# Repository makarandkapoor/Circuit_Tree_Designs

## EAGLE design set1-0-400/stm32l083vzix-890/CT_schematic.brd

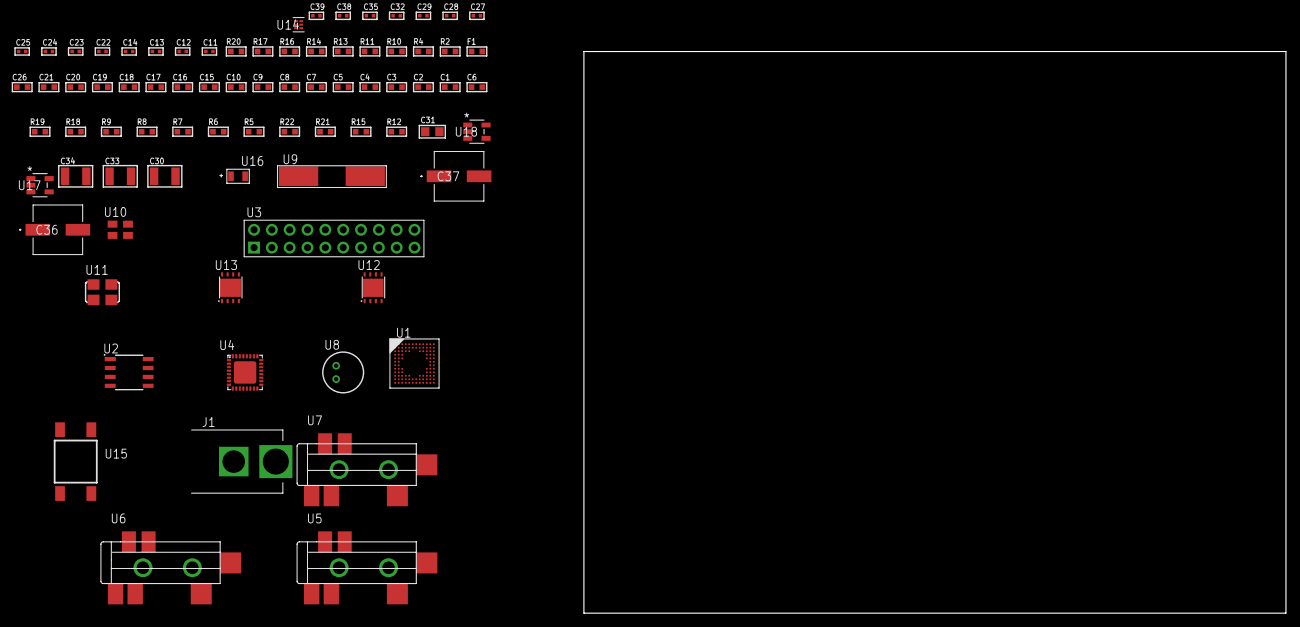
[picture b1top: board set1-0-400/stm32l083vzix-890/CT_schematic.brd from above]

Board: 2 copper layers, 100.0 x 80.0 mm, 79 parts (0 on the bottom side), 48 nets, no tracks yet.

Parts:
C1, C2, C3, C4, C5, C7, C10: 1e-07; C0603
C6: 4.7e-06; C0603
C8: 1e-08; C0603
C9, C15, C16, C17, C18, C19, C20, C21, C26: 1e-06; C0603
C11, C12: 1e-11; C0402
C13, C27, C28, C29, C32, C38, C39: 1e-08; C0402
C14, C22, C23, C24, C25, C35: 1e-07; C0402
C30, C33, C34: 1e-05; C1210
C31: 1e-05; C0805
C36, C37: 0.0001; EXV-9H
F1: 240.0; L0603
J1: PJ-037B; PJ-037B_PACKAGE
R2, R14, R17: 1000.0; R0603
R4: 4700.0; R0603
R5, R6, R7, R8, R9, R18, R19: 10000.0; R0603
R10, R11: 1270.0; R0603
R12, R15: 100000.0; R0603
R13: 200.0; R0603
R16: 2231.0; R0603
R20: 9100.0; R0603
R21: 680000.0; R0603
R22: 120000.0; R0603
U1: STM32L083VZI6; UFBGA100
U2: AT25M02-SSHD-T; SOIC-8
U3: TST-110-05-T-D-RA
U4: SGTL5000XNAA3; QFN-32
U5, U6, U7: SJ-43515TS-SMT-TR
U8: WM-64PCT; WM-64PC
U9: ABLS-25.000MHZ-B2F-T
U10: ASEK-32.768KHz-ECST; ASEK
U11: ASFL-24.57MHZ-NCS; ASFL1
U12, U13: LP3878SDX-ADJ/NOPB; WSON-8
U14: TPS3895ADRYR; SON-6
U15: 4-1437565-2; SW_4-1437565-2
U16: Q65110A2395; LGM67K-G1J2-24-Z
U17, U18: nc7sz125m5x; NC7SZ125M5X

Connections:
CLK_CRYSTAL_U1_F1: C11.1, U1.F1, U9.1
CLK_CRYSTAL_U1_G1: C12.1, U1.G1, U9.2
CLK_U1_D1: U1.D1, U10.3
CLK_U4_21: U4.21, U11.3
GND: C1.2, C2.2, C3.2, C4.2, C5.2, C6.2, C7.2, C8.2, C9.2, C10.2, C11.2, C12.2, C13.2, C14.2, C22.2, C23.2, C24.2, C25.2, C26.2, C27.2, C28.2, C29.2, C30.2, C31.2, C32.2, C33.2, C34.2, C35.2, C36.2, C37.2, C38.2, C39.2, J1.2, R2.2, R5.2, R11.2, R14.2, R17.2, R20.2, R22.2, U1.D3, U1.E3, U1.F11, U1.F12, U1.J1, U1.K1, U2.4, U3.4, U3.6, U3.8, U3.10, U3.12, U3.14, U3.16, U3.18, U3.20, U4.1, U4.3, U4.7, U4.EXP, U6.1, U7.1, U8.2, U10.2, U11.2, U12.3, U12.PAD, U13.3, U13.PAD, U14.2, U16.C, U17.2, U17.3, U18.1, U18.3
NET_U1_A4: R5.1, U1.A4
NET_U1_E2: C7.1, U1.E2
NET_U1_H2: R4.1, U1.H2, U18.4
NET_U1_M1: C8.1, C9.1, F1.1, U1.L1, U1.M1
NET_U1_M12: U15.3, U15.4
NET_U2_3: R6.1, U2.3
NET_U2_7: R8.1, U2.7
NET_U4_10: C25.1, U4.10
NET_U4_29: R10.1, U4.29
NET_U4_31: R11.1, U4.31
NET_U5_1: U4.4, U5.1
NET_U5_2: U4.2, U5.2
NET_U5_5: U4.6, U5.5
NET_U6_2: C16.1, U6.2
NET_U6_5: C15.1, U6.5
NET_U7_2: C18.1, C19.1, U7.2
NET_U7_5: C17.1, U7.5
NET_U7_13: C18.2, C19.2
NET_U8_1: C20.1, C21.1, C26.1, U4.16, U8.1
NET_U8_15: C20.2, C21.2
NET_U12_1: C29.1, U12.1
NET_U12_6: R13.2, R14.1, U12.6
NET_U12_8: R12.1, U12.8
NET_U13_1: C32.1, U13.1
NET_U13_6: R16.2, R17.1, U13.6
NET_U13_8: R15.1, U13.8
NET_U14_1: R19.1, R20.1, U14.1
NET_U14_3: R21.2, R22.1, U14.3
NET_U14_4: R18.1, U14.4, U17.4, U18.2
NET_U15_1: R2.1, U15.1, U15.2
PROC_I2S2_CK: U1.B9, U4.24
PROC_I2S2_SD: U1.B7, U4.26
PROC_I2S2_WS: U1.B3, U4.23
PROC_SPI1_MISO: U1.A7, U2.2
PROC_SPI1_MOSI: U1.A12, U2.5
PROC_SPI1_NSS: R7.1, U1.A9, U2.1
PROC_SPI1_SCK: U1.A8, U2.6
PROC_SYS_SWCLK: U1.A10, U3.9
PROC_SYS_SWDIO: U1.A11, U3.7
RST_OUT_U3_SRESET_B: R9.1, U3.15, U17.1
VCC_S1_13V1: C30.1, C33.1, C36.1, C37.1, J1.1, R12.2, R15.2, U12.4, U13.4
VCC_TIER1_1V2: C22.1, C31.1, R13.1, U4.30, U12.5
VCC_TIER1_3V3: C1.1, C2.1, C3.1, C4.1, C5.1, C6.1, C10.1, C13.1, C14.1, C23.1, C24.1, C27.1, C28.1, C34.1, C35.1, C38.1, C39.1, F1.2, R4.2, R6.2, R7.2, R8.2, R9.2, R10.2, R16.1, R18.2, R19.2, R21.1, U1.C4, U1.C11, U1.G11, U1.G12, U1.H3, U2.8, U3.1, U4.5, U4.20, U10.4, U11.4, U13.5, U14.6, U17.5, U18.5

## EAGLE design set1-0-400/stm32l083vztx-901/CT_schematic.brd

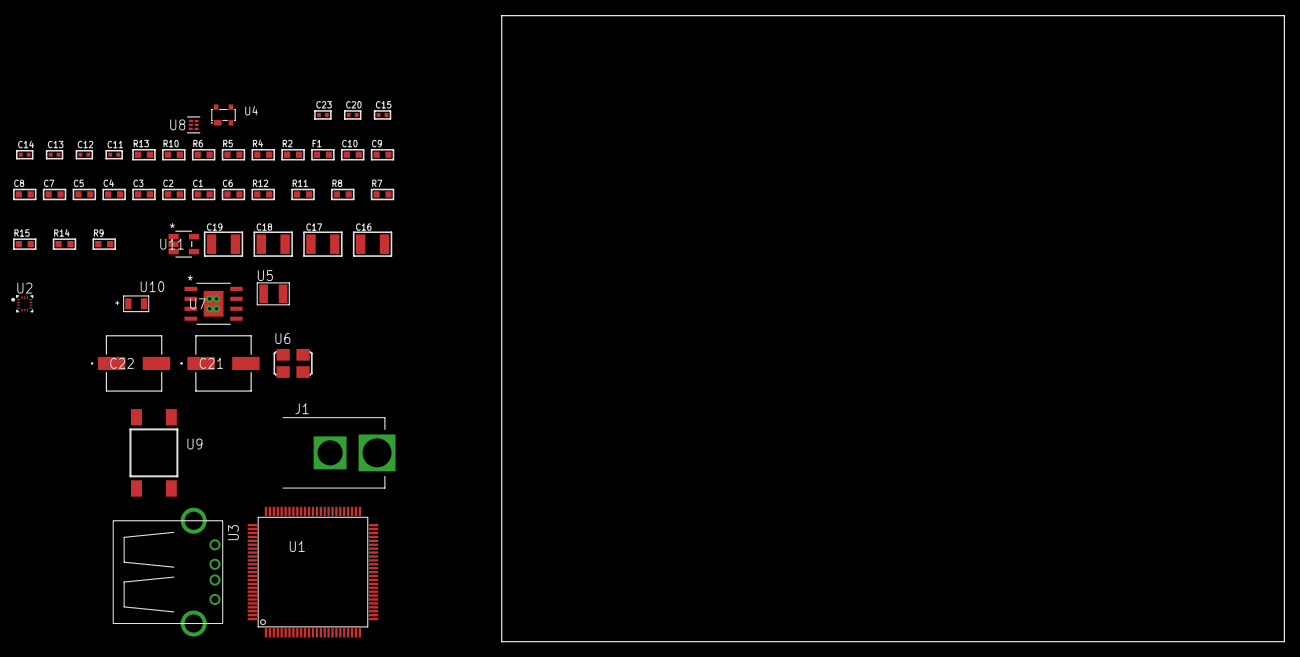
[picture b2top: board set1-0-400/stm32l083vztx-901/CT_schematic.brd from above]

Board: 2 copper layers, 100.0 x 80.0 mm, 49 parts (0 on the bottom side), 21 nets, no tracks yet.

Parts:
C1, C2, C3, C4, C5, C7, C10: 1e-07; C0603
C6: 4.7e-06; C0603
C8: 1e-08; C0603
C9: 1e-06; C0603
C11, C12: 1e-11; C0402
C13, C14, C20: 1e-07; C0402
C15, C23: 1e-08; C0402
C16, C17, C18, C19: 1e-05; C1210
C21, C22: 0.0001; EXV-9H
F1: 240.0; L0603
J1: PJ-037B; PJ-037B_PACKAGE
R2: 1000.0; R0603
R4: 4700.0; R0603
R5, R6, R10: 2200.0; R0603
R7, R8, R11, R12: 10000.0; R0603
R9: 4031.5447154472; R0603
R13: 9100.0; R0603
R14: 680000.0; R0603
R15: 120000.0; R0603
U1: STM32L083VZT6; LQFP100
U2: BMC150; LGA14R35P5X6_200X200X100
U3: 61400416021; USB-A-H
U4: prtr5v0u2ax; SOT143B
U5: ABS07-32.768KHZ-7-T
U6: ASFL1-25MHZ-NCS; ASFL1
U7: MIC5234YME; SOIC-8_EP
U8: TPS3895ADRYR; SON-6
U9: 4-1437565-2; SW_4-1437565-2
U10: Q65110A2395; LGM67K-G1J2-24-Z
U11: nc7sz125m5x; NC7SZ125M5X

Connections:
CLK_CRYSTAL_U1_8: C11.1, U1.8, U5.1
CLK_CRYSTAL_U1_9: C12.1, U1.9, U5.2
CLK_U1_12: U1.12, U6.3
GND: C1.2, C2.2, C3.2, C4.2, C5.2, C6.2, C7.2, C8.2, C9.2, C10.2, C11.2, C12.2, C13.2, C14.2, C15.2, C16.2, C17.2, C18.2, C19.2, C20.2, C21.2, C22.2, C23.2, J1.2, R2.2, R7.2, R10.2, R13.2, R15.2, U1.19, U1.20, U1.27, U1.49, U1.74, U1.99, U2.1, U2.6, U2.7, U2.9, U3.4, U3.5, U3.6, U4.1, U6.2, U7.7, U7.EPAD, U8.2, U10.C, U11.1, U11.3
NET_U1_6: C7.1, U1.6
NET_U1_14: R4.1, U1.14, U11.4
NET_U1_22: C8.1, C9.1, F1.1, U1.21, U1.22
NET_U1_68: R5.1, U1.68, U2.11
NET_U1_69: R6.1, U1.69, U2.14
NET_U1_94: R7.1, U1.94
NET_U1_98: U9.3, U9.4
NET_U4_4: U3.1, U4.4
NET_U7_4: R9.2, R10.1, U7.4
NET_U8_1: R12.1, R13.1, U8.1
NET_U8_3: R14.2, R15.1, U8.3
NET_U8_4: R11.1, U8.4, U11.2
NET_U9_1: R2.1, U9.1, U9.2
PROC_USB_DM: U1.70, U3.2, U4.3
PROC_USB_DP: U1.71, U3.3, U4.2
VCC_S1_16V3: C16.1, C17.1, C21.1, C22.1, J1.1, U7.5, U7.8
VCC_TIER1_3V3: C1.1, C2.1, C3.1, C4.1, C5.1, C6.1, C10.1, C13.1, C14.1, C15.1, C18.1, C19.1, C20.1, C23.1, F1.2, R4.2, R5.2, R6.2, R8.1, R8.2, R9.1, R11.2, R12.2, R14.1, U1.28, U1.50, U1.73, U1.75, U1.100, U2.8, U2.10, U2.12, U2.13, U6.4, U7.1, U8.6, U11.5

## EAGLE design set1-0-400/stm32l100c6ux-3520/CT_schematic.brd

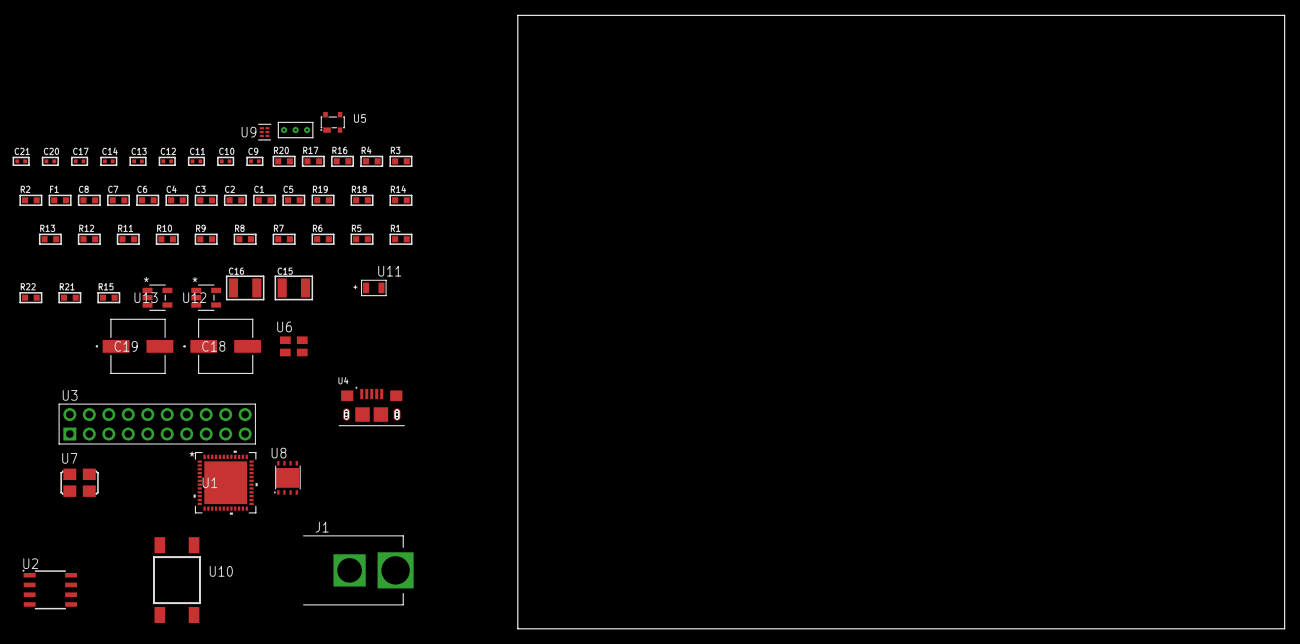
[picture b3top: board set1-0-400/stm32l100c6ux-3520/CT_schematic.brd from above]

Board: 2 copper layers, 122.6 x 80.0 mm, 59 parts (0 on the bottom side), 36 nets, no tracks yet.

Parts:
C1, C2, C3, C4, C6: 1e-07; C0603
C5: 4.7e-06; C0603
C7: 1e-08; C0603
C8: 1e-06; C0603
C9, C12, C13, C14, C20, C21: 1e-08; C0402
C10, C11, C17: 1e-07; C0402
C15, C16: 1e-05; C1210
C18, C19: 0.0001; EXV-9H
F1: 240.0; L0603
J1: PJ-037B; PJ-037B_PACKAGE
R1, R5, R6, R7, R8, R9, R10, R11, R12, R13, R14, R18, R19: 10000.0; R0603
R2, R17: 1000.0; R0603
R3: 1600.5; R0603
R4: 4700.0; R0603
R15: 100000.0; R0603
R16: 2231.0; R0603
R20: 9100.0; R0603
R21: 680000.0; R0603
R22: 120000.0; R0603
U1: STM32L100C6U6; UFQFPN48
U2: AT25640B-SSHL-T; SOIC-8
U3: TST-110-05-T-D-RA
U4: 10118193-0001LF; FCI_10118193-0001LF
U5: prtr5v0u2ax; SOT143B
U6: ASEK-32.768KHz-ECST; ASEK
U7: ASFL1-25MHZ-NCS; ASFL1
U8: LP3878SDX-ADJ/NOPB; WSON-8
U9: TPS3895ADRYR; SON-6
U10: 4-1437565-2; SW_4-1437565-2
U11: Q65110A2395; LGM67K-G1J2-24-Z
U12, U13: nc7sz125m5x; NC7SZ125M5X
U14: Dummy; DUMMY_PACKAGE_125

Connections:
CLK_U1_3: U1.3, U6.3
CLK_U1_5: U1.5, U7.3
GND: C1.2, C2.2, C3.2, C4.2, C5.2, C6.2, C7.2, C8.2, C9.2, C10.2, C11.2, C12.2, C13.2, C14.2, C15.2, C16.2, C17.2, C18.2, C19.2, C20.2, C21.2, J1.2, R2.2, R5.2, R14.2, R17.2, R20.2, R22.2, U1.8, U1.23, U1.35, U1.47, U1.49, U2.4, U3.4, U3.6, U3.8, U3.10, U3.12, U3.14, U3.16, U3.18, U3.20, U4.5, U4.6, U4.7, U4.8, U4.9, U5.1, U6.2, U7.2, U8.3, U8.PAD, U9.2, U11.C, U12.2, U12.3, U13.1, U13.3, U14.1
NET_U1_1: C6.1, U1.1
NET_U1_7: R4.1, U1.7, U13.4
NET_U1_9: C7.1, C8.1, F1.1, U1.9
NET_U1_44: R5.1, U1.44
NET_U1_45: R3.1, U1.45, U11.A
NET_U1_46: R1.1, U1.46, U10.3, U10.4
NET_U2_3: R6.1, U2.3
NET_U2_7: R8.1, U2.7
NET_U3_19: R14.1, U3.19
NET_U5_4: U4.1, U5.4
NET_U8_1: C14.1, U8.1
NET_U8_6: R16.2, R17.1, U8.6
NET_U8_8: R15.1, U8.8
NET_U9_1: R19.1, R20.1, U9.1
NET_U9_3: R21.2, R22.1, U9.3
NET_U9_4: R18.1, U9.4, U12.4, U13.2
NET_U10_1: R2.1, U10.1, U10.2
PROC_SPI1_MISO: U1.16, U2.2
PROC_SPI1_MOSI: U1.17, U2.5
PROC_SPI1_NSS: R7.1, U1.14, U2.1
PROC_SPI1_SCK: U1.15, U2.6
PROC_SYS_JTCK_SWCLK: R12.1, U1.37, U3.9
PROC_SYS_JTDI: R10.1, U1.38, U3.5
PROC_SYS_JTDO_TRACESWO: U1.39, U3.13
PROC_SYS_JTMS_SWDIO: R11.1, U1.34, U3.7
PROC_SYS_JTRST: R9.1, U1.40, U3.3
PROC_TIM2_CH1: U1.10, U14.3
PROC_TIM2_CH3: U1.12, U14.2
PROC_USB_DM: U1.32, U4.2, U5.3
PROC_USB_DP: U1.33, U4.3, U5.2
RST_OUT_U3_SRESET_B: R13.1, U3.15, U12.1
VCC_S1_15V6: C15.1, C18.1, C19.1, J1.1, R15.2, U8.4
VCC_TIER1_3V3: C1.1, C2.1, C3.1, C4.1, C5.1, C9.1, C10.1, C11.1, C12.1, C13.1, C16.1, C17.1, C20.1, C21.1, F1.2, R1.2, R3.2, R4.2, R6.2, R7.2, R8.2, R9.2, R10.2, R11.2, R12.2, R13.2, R16.1, R18.2, R19.2, R21.1, U1.24, U1.36, U1.48, U2.8, U3.1, U3.2, U6.4, U7.4, U8.5, U9.6, U12.5, U13.5

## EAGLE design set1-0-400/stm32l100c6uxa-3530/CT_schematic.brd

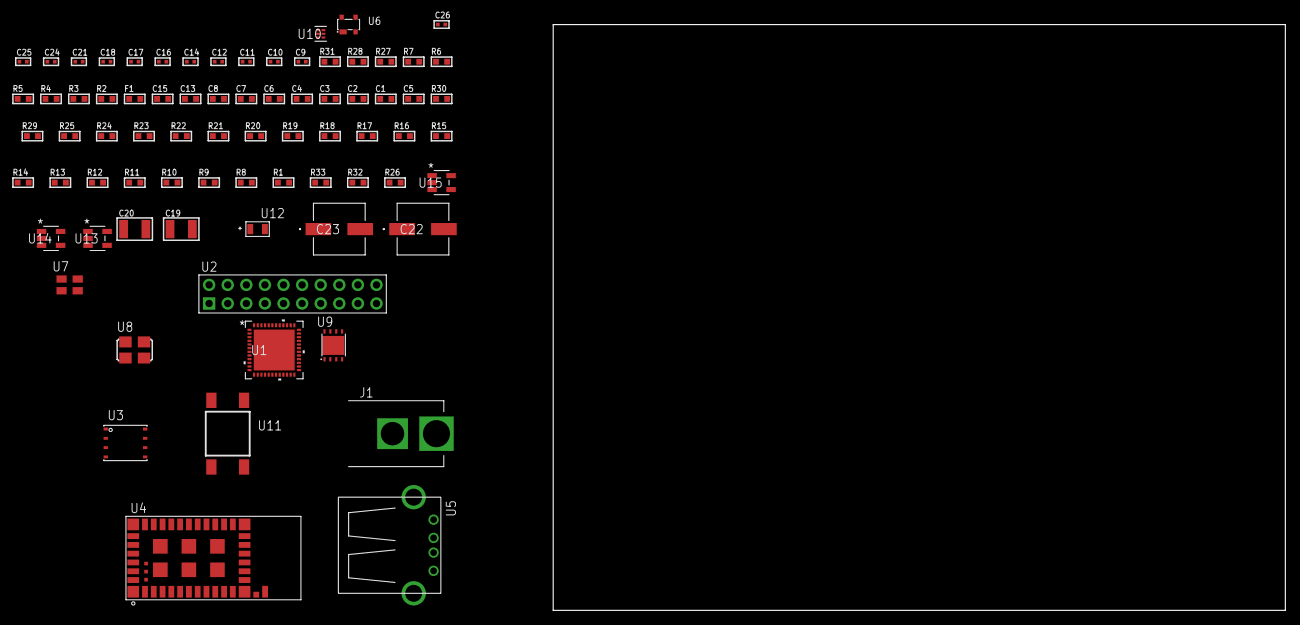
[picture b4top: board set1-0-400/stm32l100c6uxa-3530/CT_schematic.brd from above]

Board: 2 copper layers, 100.0 x 80.0 mm, 76 parts (0 on the bottom side), 42 nets, no tracks yet.

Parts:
C1, C2, C3, C4, C6: 1e-07; C0603
C5: 4.7e-06; C0603
C7: 1e-08; C0603
C8, C13, C15: 1e-06; C0603
C9, C10, C12, C14, C21: 1e-07; C0402
C11, C16, C17, C18, C24, C25, C26: 1e-08; C0402
C19, C20: 1e-05; C1210
C22, C23: 0.0001; EXV-9H
F1: 240.0; L0603
J1: PJ-037B; PJ-037B_PACKAGE
R1, R8, R9, R10, R11, R12, R13, R14, R15, R16, R17, R18, R25, R29, R30: 10000.0; R0603
R2, R28: 1000.0; R0603
R3: 1600.5; R0603
R4, R5: 4700.0; R0603
R6, R7: 2200.0; R0603
R19, R20, R21, R22, R23, R24: 34000.0; R0603
R26: 100000.0; R0603
R27: 2231.0; R0603
R31: 9100.0; R0603
R32: 680000.0; R0603
R33: 120000.0; R0603
U1: STM32L100C6U6A; UFQFPN48
U2: TST-110-05-T-D-RA
U3: 24AA512-I/MF; DFN8-S
U4: 88-00153-02
U5: 61400416021; USB-A-H
U6: prtr5v0u2ax; SOT143B
U7: ASEK-32.768KHz-ECST; ASEK
U8: ASFL1-25MHZ-NCS; ASFL1
U9: LP3878SDX-ADJ/NOPB; WSON-8
U10: TPS3895ADRYR; SON-6
U11: 4-1437565-2; SW_4-1437565-2
U12: Q65110A2395; LGM67K-G1J2-24-Z
U13, U14, U15: nc7sz125m5x; NC7SZ125M5X

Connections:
CLK_U1_3: U1.3, U7.3
CLK_U1_5: U1.5, U8.3
GND: C1.2, C2.2, C3.2, C4.2, C5.2, C6.2, C7.2, C8.2, C9.2, C10.2, C11.2, C12.2, C13.2, C14.2, C15.2, C16.2, C17.2, C18.2, C19.2, C20.2, C21.2, C22.2, C23.2, C24.2, C25.2, C26.2, J1.2, R2.2, R8.2, R14.2, R15.2, R16.2, R28.2, R31.2, R33.2, U1.8, U1.23, U1.35, U1.47, U1.49, U2.4, U2.6, U2.8, U2.10, U2.12, U2.14, U2.16, U2.18, U2.20, U3.4, U3.7, U4.1, U4.9, U4.13, U4.14, U4.15, U4.16, U4.17, U4.18, U4.19, U4.20, U4.21, U4.22, U4.23, U4.24, U4.25, U4.26, U4.27, U4.31, U4.32, U4.39, U4.40, U4.41, U4.42, U4.43, U4.44, U4.49, U5.4, U5.5, U5.6, U6.1, U7.2, U8.2, U9.3, U9.PAD, U10.2, U12.C, U13.2, U13.3, U14.1, U14.3, U15.1, U15.3
NET_U1_1: C6.1, U1.1
NET_U1_7: R5.1, U1.7, U15.4
NET_U1_9: C7.1, C8.1, F1.1, U1.9
NET_U1_42: R6.1, U1.42, U3.6
NET_U1_43: R7.1, U1.43, U3.5
NET_U1_44: R8.1, U1.44
NET_U1_45: R3.1, U1.45, U12.A
NET_U1_46: R1.1, U1.46, U11.3, U11.4
NET_U2_19: R14.1, U2.19
NET_U3_1: R15.1, U3.1
NET_U3_2: R16.1, U3.2
NET_U3_3: R17.1, U3.3
NET_U4_2: R21.1, U4.2
NET_U4_6: R25.1, U4.6
NET_U4_10: R4.1, U4.10, U14.4
NET_U4_11: R18.1, U4.11
NET_U4_34: R20.1, U4.34
NET_U6_4: U5.1, U6.4
NET_U9_1: C18.1, U9.1
NET_U9_6: R27.2, R28.1, U9.6
NET_U9_8: R26.1, U9.8
NET_U10_1: R30.1, R31.1, U10.1
NET_U10_3: R32.2, R33.1, U10.3
NET_U10_4: R29.1, U10.4, U13.4, U14.2, U15.2
NET_U11_1: R2.1, U11.1, U11.2
PROC_SPI1_MISO: R19.1, U1.16, U4.35
PROC_SPI1_MOSI: R23.1, U1.17, U4.37
PROC_SPI1_NSS: R22.1, U1.14, U4.38
PROC_SPI1_SCK: R24.1, U1.15, U4.36
PROC_SYS_JTCK_SWCLK: R12.1, U1.37, U2.9
PROC_SYS_JTDI: R10.1, U1.38, U2.5
PROC_SYS_JTDO_TRACESWO: U1.39, U2.13
PROC_SYS_JTMS_SWDIO: R11.1, U1.34, U2.7
PROC_SYS_JTRST: R9.1, U1.40, U2.3
PROC_USB_DM: U1.32, U5.2, U6.3
PROC_USB_DP: U1.33, U5.3, U6.2
RST_OUT_U2_SRESET_B: R13.1, U2.15, U13.1
VCC_S1_14V6: C19.1, C22.1, C23.1, J1.1, R26.2, U9.4
VCC_TIER1_3V3: C1.1, C2.1, C3.1, C4.1, C5.1, C9.1, C10.1, C11.1, C12.1, C13.1, C14.1, C15.1, C16.1, C17.1, C20.1, C21.1, C24.1, C25.1, C26.1, F1.2, R1.2, R3.2, R4.2, R5.2, R6.2, R7.2, R9.2, R10.2, R11.2, R12.2, R13.2, R17.2, R18.2, R19.2, R20.2, R21.2, R22.2, R23.2, R24.2, R25.2, R27.1, R29.2, R30.2, R32.1, U1.24, U1.36, U1.48, U2.1, U2.2, U3.8, U4.12, U4.33, U7.4, U8.4, U9.5, U10.6, U13.5, U14.5, U15.5

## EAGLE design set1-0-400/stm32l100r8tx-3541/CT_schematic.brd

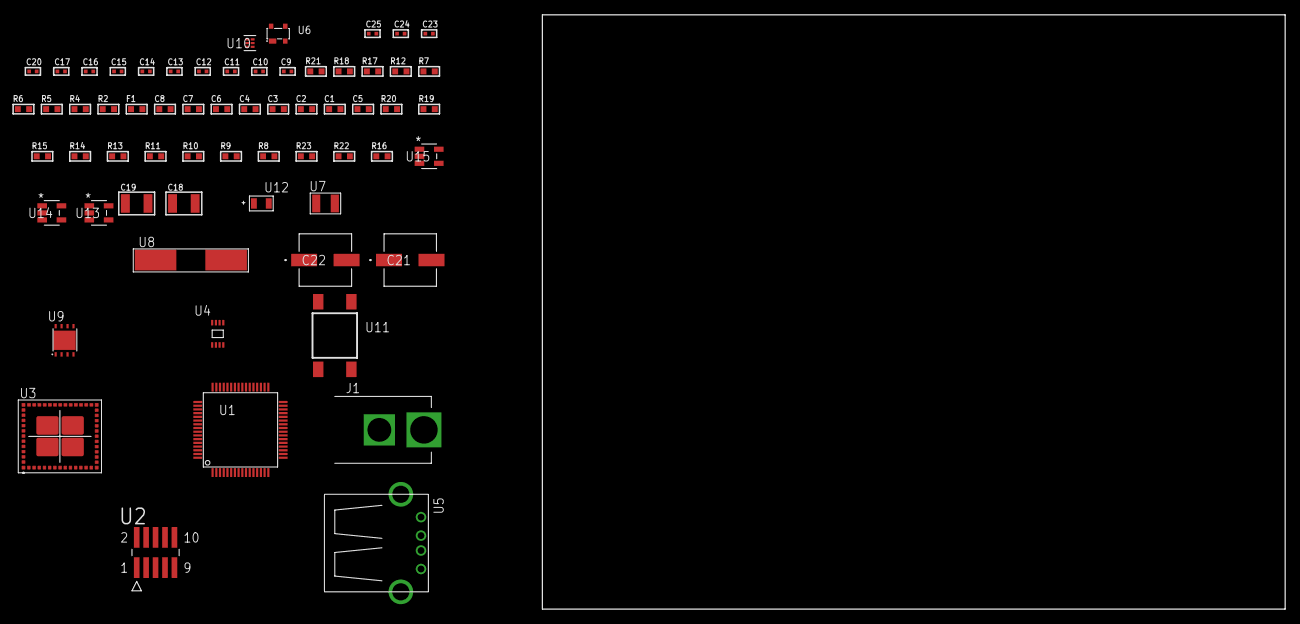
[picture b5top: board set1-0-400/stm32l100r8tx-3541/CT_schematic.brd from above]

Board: 2 copper layers, 100.0 x 80.0 mm, 63 parts (0 on the bottom side), 37 nets, no tracks yet.

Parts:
C1, C2, C3, C4, C6: 1e-07; C0603
C5: 4.7e-06; C0603
C7: 1e-08; C0603
C8: 1e-06; C0603
C9, C10, C11, C12: 1e-11; C0402
C13, C14, C15, C20: 1e-07; C0402
C16, C17, C23, C24, C25: 1e-08; C0402
C18, C19: 1e-05; C1210
C21, C22: 0.0001; EXV-9H
F1: 240.0; L0603
J1: PJ-037B; PJ-037B_PACKAGE
R2, R18: 1000.0; R0603
R4, R5: 4700.0; R0603
R6, R7: 2200.0; R0603
R8, R9, R10, R11, R13, R14, R15, R19, R20: 10000.0; R0603
R12: 5.0; R0603
R16: 100000.0; R0603
R17: 2231.0; R0603
R21: 9100.0; R0603
R22: 680000.0; R0603
R23: 120000.0; R0603
U1: STM32L100R8T6; LQFP64
U2: FTSH-105-01-L-DV-K; SAMTEC_FTSH-105-01-L-DV-K
U3: MBH7BLZ02-109004
U4: 24AA32AT-I/MNY; TDFN-8/6MM
U5: 61400416021; USB-A-H
U6: prtr5v0u2ax; SOT143B
U7: ABS07-32.768KHZ-7-T
U8: ABLS-25.000MHZ-B2F-T
U9: LP3878SDX-ADJ/NOPB; WSON-8
U10: TPS3895ADRYR; SON-6
U11: 4-1437565-2; SW_4-1437565-2
U12: Q65110A2395; LGM67K-G1J2-24-Z
U13, U14, U15: nc7sz125m5x; NC7SZ125M5X

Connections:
CLK_CRYSTAL_U1_3: C9.1, U1.3, U7.1
CLK_CRYSTAL_U1_4: C10.1, U1.4, U7.2
CLK_CRYSTAL_U1_5: C11.1, U1.5, U8.1
CLK_CRYSTAL_U1_6: C12.1, U1.6, U8.2
GND: C1.2, C2.2, C3.2, C4.2, C5.2, C6.2, C7.2, C8.2, C9.2, C10.2, C11.2, C12.2, C13.2, C14.2, C15.2, C16.2, C17.2, C18.2, C19.2, C20.2, C21.2, C22.2, C23.2, C24.2, C25.2, J1.2, R2.2, R8.2, R12.2, R18.2, R21.2, R23.2, U1.12, U1.18, U1.31, U1.47, U1.63, U2.3, U2.5, U3.1, U3.3, U3.15, U3.27, U3.29, U3.41, U3.42, U3.43, U3.44, U3.45, U3.46, U3.47, U3.48, U3.49, U3.50, U3.52, U3.53, U3.54, U3.55, U3.56, U4.4, U4.7, U5.4, U5.5, U5.6, U6.1, U9.3, U9.PAD, U10.2, U12.C, U13.2, U13.3, U14.1, U14.3, U15.1, U15.3
NET_U1_1: C6.1, U1.1
NET_U1_7: R5.1, U1.7, U15.4
NET_U1_13: C7.1, C8.1, F1.1, U1.13
NET_U1_58: R6.1, U1.58, U4.6
NET_U1_59: R7.1, U1.59, U4.5
NET_U1_60: R8.1, U1.60
NET_U1_62: U11.3, U11.4
NET_U2_9: R12.1, U2.9
NET_U3_39: R4.1, U3.39, U14.4
NET_U4_1: R13.1, U4.1
NET_U4_2: R14.1, U4.2
NET_U4_3: R15.1, U4.3
NET_U6_4: U5.1, U6.4
NET_U9_1: C17.1, U9.1
NET_U9_6: R17.2, R18.1, U9.6
NET_U9_8: R16.1, U9.8
NET_U10_1: R20.1, R21.1, U10.1
NET_U10_3: R22.2, R23.1, U10.3
NET_U10_4: R19.1, U10.4, U13.4, U14.2, U15.2
NET_U11_1: R2.1, U11.1, U11.2
PROC_SYS_JTCK_SWCLK: R10.1, U1.49, U2.4
PROC_SYS_JTDO_TRACESWO: U1.55, U2.6
PROC_SYS_JTMS_SWDIO: R11.1, U1.46, U2.2
PROC_USART2_CTS: U1.14, U3.26
PROC_USART2_RTS: U1.15, U3.24
PROC_USART2_RX: U1.17, U3.25
PROC_USART2_TX: U1.16, U3.23
PROC_USB_DM: U1.44, U5.2, U6.3
PROC_USB_DP: U1.45, U5.3, U6.2
RST_OUT_U2_JTAG_RST_B: R9.1, U2.10, U13.1
VCC_S1_16V0: C18.1, C21.1, C22.1, J1.1, R16.2, U9.4
VCC_TIER1_3V3: C1.1, C2.1, C3.1, C4.1, C5.1, C13.1, C14.1, C15.1, C16.1, C19.1, C20.1, C23.1, C24.1, C25.1, F1.2, R4.2, R5.2, R6.2, R7.2, R9.2, R10.2, R11.2, R13.2, R14.2, R15.2, R17.1, R19.2, R20.2, R22.1, U1.19, U1.32, U1.48, U1.64, U2.1, U3.28, U4.8, U9.5, U10.6, U13.5, U14.5, U15.5

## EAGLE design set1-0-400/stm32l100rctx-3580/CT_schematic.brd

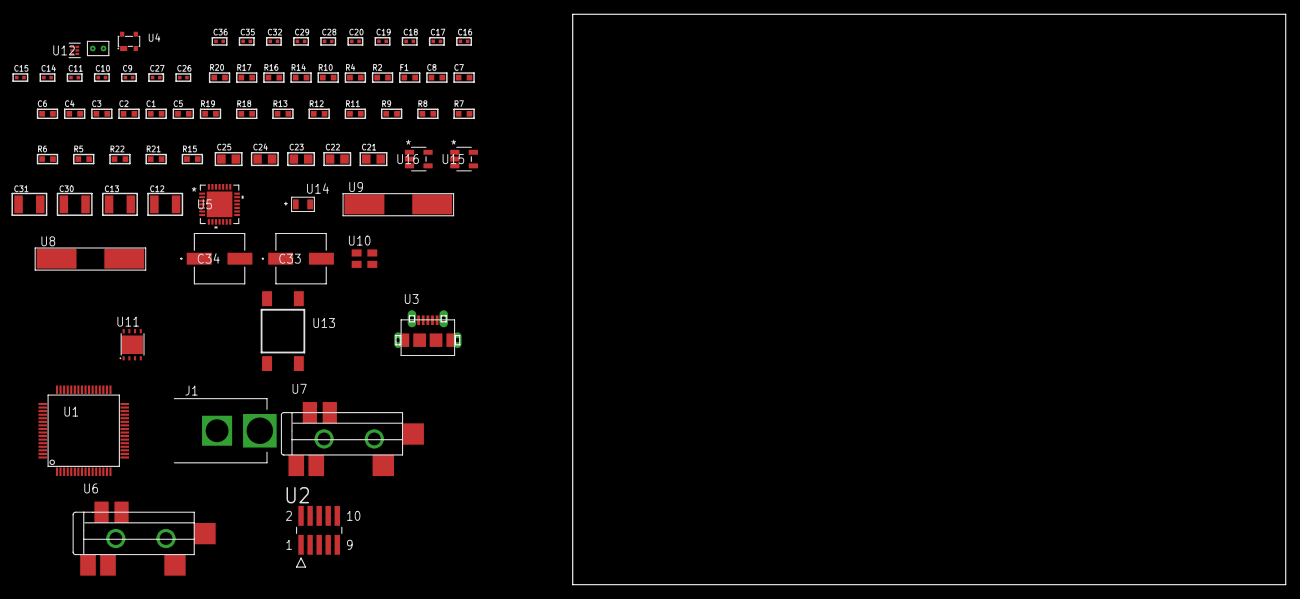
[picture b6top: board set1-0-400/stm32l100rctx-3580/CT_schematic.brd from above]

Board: 2 copper layers, 124.8 x 80.0 mm, 75 parts (0 on the bottom side), 37 nets, no tracks yet.

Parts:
C1, C2, C3, C4, C6: 1e-07; C0603
C5: 4.7e-06; C0603
C7: 1e-08; C0603
C8: 1e-06; C0603
C9, C10: 1e-11; C0402
C11, C16, C17, C18, C19, C20, C32: 1e-07; C0402
C12, C13: 2.2e-05; C1210
C14, C15: 1e-09; C0402
C21, C22, C23, C24, C25: 1e-05; C0805
C26, C27: 2.2e-11; C0402
C28, C29, C35, C36: 1e-08; C0402
C30, C31: 1e-05; C1210
C33, C34: 0.0001; EXV-9H
F1: 240.0; L0603
J1: PJ-037B; PJ-037B_PACKAGE
R2, R17: 1000.0; R0603
R4: 4700.0; R0603
R5, R6, R7, R8, R9, R18, R19: 10000.0; R0603
R10: 5.0; R0603
R11, R12, R13: 47000.0; R0603
R14: 680.0; R0603
R15: 100000.0; R0603
R16: 2231.0; R0603
R20: 9100.0; R0603
R21: 680000.0; R0603
R22: 120000.0; R0603
U1: STM32L100RCT6; LQFP64
U2: FTSH-105-01-L-DV-K; SAMTEC_FTSH-105-01-L-DV-K
U3: 47590-0001; MICRO_USB_AB
U4: prtr5v0u2ax; SOT143B
U5: WM8731CLSEFL; QFN-28
U6, U7: SJ-43515TS-SMT-TR
U8: ABLS-25.000MHZ-B2F-T
U9: ABLS-12.288MHZ-B4-T
U10: ASEK-32.768KHz-ECST; ASEK
U11: LP3878SDX-ADJ/NOPB; WSON-8
U12: TPS3895ADRYR; SON-6
U13: 4-1437565-2; SW_4-1437565-2
U14: Q65110A2395; LGM67K-G1J2-24-Z
U15, U16: nc7sz125m5x; NC7SZ125M5X
U17: Dummy; DUMMY_PACKAGE_156

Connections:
CLK_CRYSTAL_U1_5: C9.1, U1.5, U8.1
CLK_CRYSTAL_U1_6: C10.1, U1.6, U8.2
CLK_CRYSTAL_U5_1: C26.1, U5.1, U9.1
CLK_CRYSTAL_U5_2: C27.1, U5.2, U9.2
CLK_U1_3: U1.3, U10.3
GND: C1.2, C2.2, C3.2, C4.2, C5.2, C6.2, C7.2, C8.2, C9.2, C10.2, C11.2, C15.2, C16.2, C17.2, C18.2, C19.2, C20.2, C21.2, C22.2, C23.2, C24.2, C25.2, C26.2, C27.2, C28.2, C29.2, C30.2, C31.2, C32.2, C33.2, C34.2, C35.2, C36.2, J1.2, R2.2, R5.2, R9.2, R10.2, R11.2, R12.2, R13.2, R17.2, R20.2, R22.2, U1.12, U1.18, U1.31, U1.47, U1.63, U2.3, U2.5, U3.5, U3.6, U3.7, U3.8, U3.9, U4.1, U5.4, U5.15, U5.19, U5.25, U5.26, U5.29, U6.1, U7.1, U10.2, U11.3, U11.PAD, U12.2, U14.C, U15.2, U15.3, U16.1, U16.3, U17.1
NET_U1_1: C6.1, U1.1
NET_U1_7: R4.1, U1.7, U16.4
NET_U1_13: C7.1, C8.1, F1.1, U1.13
NET_U1_60: R5.1, U1.60
NET_U1_62: U13.3, U13.4
NET_U2_9: R10.1, U2.9
NET_U4_4: U3.1, U4.4
NET_U5_20: C20.1, C25.1, U5.20
NET_U6_2: C13.1, R12.1, U6.2
NET_U6_5: C12.1, R11.1, U6.5
NET_U7_5: C14.1, C15.1, R13.1, R14.1, U7.5
NET_U11_1: C29.1, U11.1
NET_U11_6: R16.2, R17.1, U11.6
NET_U11_8: R15.1, U11.8
NET_U12_1: R19.1, R20.1, U12.1
NET_U12_3: R21.2, R22.1, U12.3
NET_U12_4: R18.1, U12.4, U15.4, U16.2
NET_U13_1: R2.1, U13.1, U13.2
PROC_DAC_OUT2: U1.21, U17.2
PROC_I2S2_CK: U1.34, U5.7
PROC_I2S2_SD: U1.36, U5.8
PROC_I2S2_WS: U1.33, U5.9, U5.11
PROC_SYS_JTCK_SWCLK: R9.1, U1.49, U2.4
PROC_SYS_JTDI: R7.1, U1.50, U2.8
PROC_SYS_JTDO_TRACESWO: U1.55, U2.6
PROC_SYS_JTMS_SWDIO: R8.1, U1.46, U2.2
PROC_USB_DM: U1.44, U3.2, U4.3
PROC_USB_DP: U1.45, U3.3, U4.2
RST_OUT_U2_JTAG_RST_B: R6.1, U2.10, U15.1
VCC_S1_14V0: C30.1, C33.1, C34.1, J1.1, R15.2, U11.4
VCC_TIER1_3V3: C1.1, C2.1, C3.1, C4.1, C5.1, C11.1, C16.1, C17.1, C18.1, C19.1, C21.1, C22.1, C23.1, C24.1, C28.1, C31.1, C32.1, C35.1, C36.1, F1.2, R4.2, R6.2, R7.2, R8.2, R16.1, R18.2, R19.2, R21.1, U1.19, U1.32, U1.48, U1.64, U2.1, U5.3, U5.5, U5.12, U5.18, U10.4, U11.5, U12.6, U15.5, U16.5

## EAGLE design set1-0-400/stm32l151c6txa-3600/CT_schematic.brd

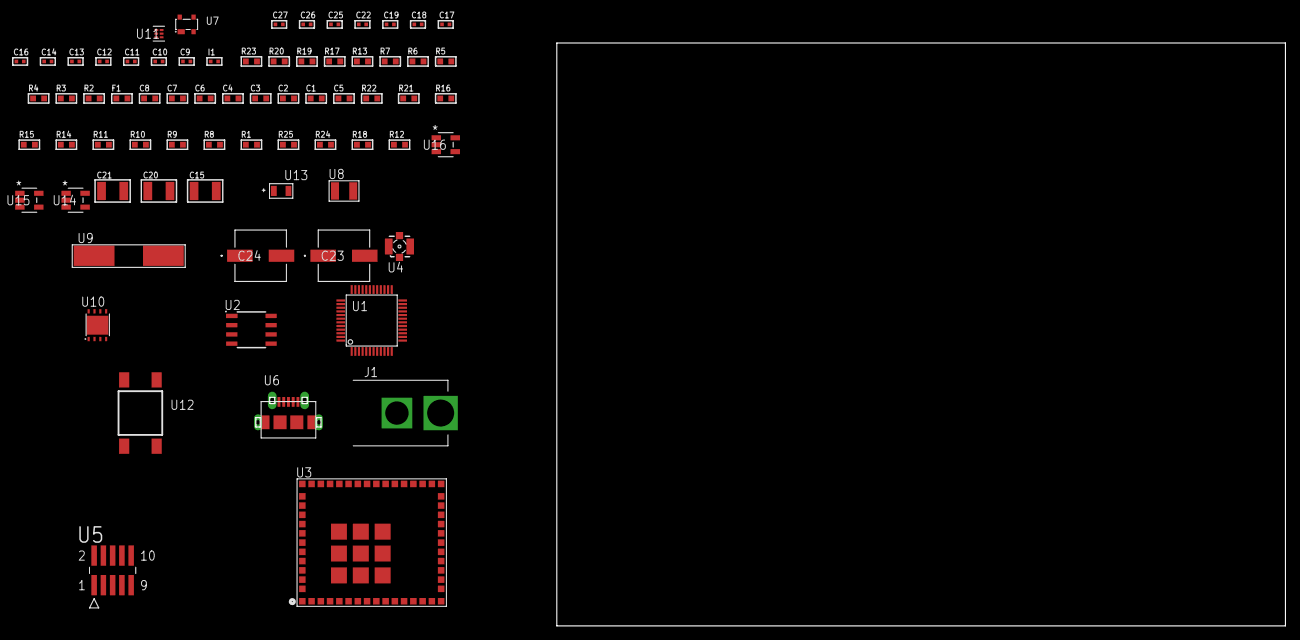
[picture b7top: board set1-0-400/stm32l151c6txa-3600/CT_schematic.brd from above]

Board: 2 copper layers, 71 parts (0 on the bottom side), 40 nets, no tracks yet.

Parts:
C1, C2, C3, C4, C6: 1e-07; C0603
C5: 4.7e-06; C0603
C7: 1e-08; C0603
C8: 1e-06; C0603
C9, C10, C11, C12: 1e-11; C0402
C13, C19, C25, C26, C27: 1e-08; C0402
C14: 1e-12; C0402
C15: 2.2e-05; C1210
C16, C17, C18, C22: 1e-07; C0402
C20, C21: 1e-05; C1210
C23, C24: 0.0001; EXV-9H
F1: 240.0; L0603
I1: 3.6e-09; C0402
J1: PJ-037B; PJ-037B_PACKAGE
R1, R8, R9, R10, R11, R14, R15, R16, R21, R22: 10000.0; R0603
R2, R20: 1000.0; R0603
R3: 1600.5; R0603
R4, R5: 4700.0; R0603
R6, R7: 2200.0; R0603
R12, R18: 100000.0; R0603
R13: 2700.0; R0603
R17: 5.0; R0603
R19: 2231.0; R0603
R23: 9100.0; R0603
R24: 680000.0; R0603
R25: 120000.0; R0603
U1: STM32L151C6T6A; LQFP48
U2: AT25128B-SSHL-T; SOIC-8
U3: CC3200MODR1M2AMOBT; LGA63S127P16X13_2050X1750X150
U4: 73412-0114; COAXIAL_C
U5: FTSH-105-01-L-DV-K; SAMTEC_FTSH-105-01-L-DV-K
U6: 47590-0001; MICRO_USB_AB
U7: prtr5v0u2ax; SOT143B
U8: ABS07-32.768KHZ-7-T
U9: ABLS-25.000MHZ-B2F-T
U10: LP3878SDX-ADJ/NOPB; WSON-8
U11: TPS3895ADRYR; SON-6
U12: 4-1437565-2; SW_4-1437565-2
U13: Q65110A2395; LGM67K-G1J2-24-Z
U14, U15, U16: nc7sz125m5x; NC7SZ125M5X

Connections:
CLK_CRYSTAL_U1_3: C9.1, U1.3, U8.1
CLK_CRYSTAL_U1_4: C10.1, U1.4, U8.2
CLK_CRYSTAL_U1_5: C11.1, U1.5, U9.1
CLK_CRYSTAL_U1_6: C12.1, U1.6, U9.2
GND: C1.2, C2.2, C3.2, C4.2, C5.2, C6.2, C7.2, C8.2, C9.2, C10.2, C11.2, C12.2, C13.2, C14.2, C15.2, C16.2, C17.2, C18.2, C19.2, C20.2, C21.2, C22.2, C23.2, C24.2, C25.2, C26.2, C27.2, J1.2, R2.2, R8.2, R12.2, R13.2, R17.2, R20.2, R23.2, R25.2, U1.8, U1.23, U1.35, U1.47, U2.4, U3.1, U3.2, U3.16, U3.27, U3.28, U3.30, U3.32, U3.38, U3.43, U3.55, U3.56, U3.57, U3.58, U3.59, U3.60, U3.61, U3.62, U3.63, U4.1, U4.2, U4.3, U4.4, U5.3, U5.5, U6.5, U6.6, U6.7, U6.8, U6.9, U7.1, U10.3, U10.PAD, U11.2, U13.C, U14.2, U14.3, U15.1, U15.3, U16.1, U16.3
NET_U1_1: C6.1, U1.1
NET_U1_7: R5.1, U1.7, U16.4
NET_U1_9: C7.1, C8.1, F1.1, U1.9
NET_U1_42: R6.1, U1.42, U3.3
NET_U1_43: R7.1, U1.43, U3.4
NET_U1_44: R8.1, U1.44
NET_U1_45: R3.1, U1.45, U13.A
NET_U1_46: R1.1, U1.46, U12.3, U12.4
NET_U2_3: R9.1, U2.3
NET_U2_7: R11.1, U2.7
NET_U3_21: R12.1, U3.21
NET_U3_23: R13.1, U3.23
NET_U3_35: R4.1, U3.35, U15.4
NET_U4_1: C14.1, I1.1, U4.1
NET_U5_9: R17.1, U5.9
NET_U7_4: U6.1, U7.4
NET_U10_1: C19.1, U10.1
NET_U10_6: R19.2, R20.1, U10.6
NET_U10_8: R18.1, U10.8
NET_U11_1: R22.1, R23.1, U11.1
NET_U11_3: R24.2, R25.1, U11.3
NET_U11_4: R21.1, U11.4, U14.4, U15.2, U16.2
NET_U12_1: R2.1, U12.1, U12.2
PROC_SPI1_MISO: U1.16, U2.2
PROC_SPI1_MOSI: U1.17, U2.5
PROC_SPI1_NSS: R10.1, U1.14, U2.1
PROC_SPI1_SCK: U1.15, U2.6
PROC_SYS_JTCK_SWCLK: R15.1, U1.37, U5.4
PROC_SYS_JTDO_TRACESWO: U1.39, U5.6
PROC_SYS_JTMS_SWDIO: R16.1, U1.34, U5.2
PROC_USB_DM: U1.32, U6.2, U7.3
PROC_USB_DP: U1.33, U6.3, U7.2
RST_OUT_U5_JTAG_RST_B: R14.1, U5.10, U14.1
VCC_S1_11V8: C20.1, C23.1, C24.1, J1.1, R18.2, U10.4
VCC_TIER1_3V3: C1.1, C2.1, C3.1, C4.1, C5.1, C13.1, C15.1, C16.1, C17.1, C18.1, C21.1, C22.1, C25.1, C26.1, C27.1, F1.2, R1.2, R3.2, R4.2, R5.2, R6.2, R7.2, R9.2, R10.2, R11.2, R14.2, R15.2, R16.2, R19.1, R21.2, R22.2, R24.1, U1.24, U1.36, U1.48, U2.8, U3.36, U3.37, U3.40, U5.1, U10.5, U11.6, U14.5, U15.5, U16.5

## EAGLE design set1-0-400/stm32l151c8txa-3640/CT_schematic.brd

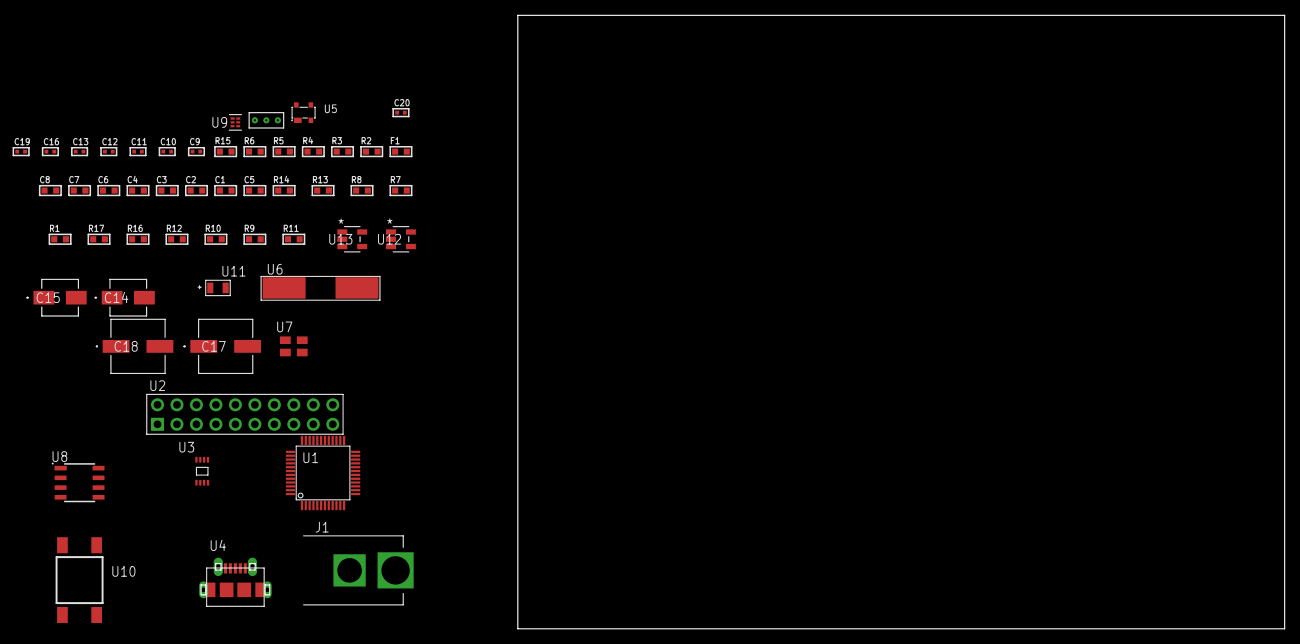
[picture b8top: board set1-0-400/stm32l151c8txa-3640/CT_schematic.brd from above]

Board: 2 copper layers, 53 parts (0 on the bottom side), 30 nets, no tracks yet.

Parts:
C1, C2, C3, C4, C6: 1e-07; C0603
C5: 4.7e-06; C0603
C7: 1e-08; C0603
C8: 1e-06; C0603
C9, C10: 1e-11; C0402
C11, C16: 1e-07; C0402
C12, C13, C19, C20: 1e-08; C0402
C14: 1e-06; EXV-9B
C15: 2.2e-06; EXV-9B
C17, C18: 0.0001; EXV-9H
F1: 240.0; L0603
J1: PJ-037B; PJ-037B_PACKAGE
R1, R7, R8, R13, R14: 10000.0; R0603
R2: 1000.0; R0603
R3: 1600.5; R0603
R4: 4700.0; R0603
R5, R6: 2200.0; R0603
R9, R10, R12: 100000.0; R0603
R11: 164658.62; R0603
R15: 9100.0; R0603
R16: 680000.0; R0603
R17: 120000.0; R0603
U1: STM32L151C8T6A; LQFP48
U2: TST-110-05-T-D-RA
U3: 24AA01T-I/MNY; TDFN-8/6MM
U4: 47590-0001; MICRO_USB_AB
U5: prtr5v0u2ax; SOT143B
U6: ABLS-25.000MHZ-B2F-T
U7: ASEK-32.768KHz-ECST; ASEK
U8: LP2954AIMX/NOPB; LP2954
U9: TPS3895ADRYR; SON-6
U10: 4-1437565-2; SW_4-1437565-2
U11: Q65110A2395; LGM67K-G1J2-24-Z
U12, U13: nc7sz125m5x; NC7SZ125M5X
U14: Dummy; DUMMY_PACKAGE_110

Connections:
CLK_CRYSTAL_U1_5: C9.1, U1.5, U6.1
CLK_CRYSTAL_U1_6: C10.1, U1.6, U6.2
CLK_U1_3: U1.3, U7.3
GND: C1.2, C2.2, C3.2, C4.2, C5.2, C6.2, C7.2, C8.2, C9.2, C10.2, C11.2, C12.2, C13.2, C14.2, C15.2, C16.2, C17.2, C18.2, C19.2, C20.2, J1.2, R2.2, R7.2, R12.2, R15.2, R17.2, U1.8, U1.23, U1.35, U1.47, U2.4, U2.6, U2.8, U2.10, U2.12, U2.14, U2.16, U2.18, U2.20, U3.4, U4.5, U4.6, U4.7, U4.8, U4.9, U5.1, U7.2, U8.4, U9.2, U11.C, U12.2, U12.3, U13.1, U13.3, U14.1
NET_U1_1: C6.1, U1.1
NET_U1_7: R4.1, U1.7, U13.4
NET_U1_9: C7.1, C8.1, F1.1, U1.9
NET_U1_42: R5.1, U1.42, U3.6
NET_U1_43: R6.1, U1.43, U3.5
NET_U1_44: R7.1, U1.44
NET_U1_45: R3.1, U1.45, U11.A
NET_U1_46: R1.1, U1.46, U10.3, U10.4
NET_U5_4: U4.1, U5.4
NET_U8_3: R10.1, U8.3
NET_U8_5: R9.1, U8.5
NET_U8_7: R11.2, R12.1, U8.7
NET_U9_1: R14.1, R15.1, U9.1
NET_U9_3: R16.2, R17.1, U9.3
NET_U9_4: R13.1, U9.4, U12.4, U13.2
NET_U10_1: R2.1, U10.1, U10.2
PROC_PC13_WKUP2: U1.2, U14.2
PROC_PC15_OSC32_OUT: U1.4, U14.3
PROC_SYS_JTCK_SWCLK: U1.37, U2.9
PROC_SYS_JTDO_TRACESWO: U1.39, U2.13
PROC_SYS_JTMS_SWDIO: U1.34, U2.7
PROC_USB_DM: U1.32, U4.2, U5.3
PROC_USB_DP: U1.33, U4.3, U5.2
RST_OUT_U2_SRESET_B: R8.1, U2.15, U12.1
VCC_S1_6V7: C14.1, C17.1, C18.1, J1.1, R10.2, U8.8
VCC_TIER1_3V3: C1.1, C2.1, C3.1, C4.1, C5.1, C11.1, C12.1, C13.1, C15.1, C16.1, C19.1, C20.1, F1.2, R1.2, R3.2, R4.2, R5.2, R6.2, R8.2, R9.2, R11.1, R13.2, R14.2, R16.1, U1.24, U1.36, U1.48, U2.1, U3.7, U3.8, U7.4, U8.1, U9.6, U12.5, U13.5
